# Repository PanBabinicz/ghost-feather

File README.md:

# Ghost Feather

> [!NOTE]
> **Please bear in mind that the workspace was primarily created for enjoyment
> and educational endeavors.**

> The MIT License (MIT)
>
> Copyright (c) 2011-2024 The Bootstrap Authors
>
> Permission is hereby granted, free of charge, to any person obtaining a copy
> of this software and associated documentation files (the "Software"), to deal
> in the Software without restriction, including without limitation the rights
> to use, copy, modify, merge, publish, distribute, sublicense, and/or sell
> copies of the Software, and to permit persons to whom the Software is
> furnished to do so, subject to the following conditions:
>
> The above copyright notice and this permission notice shall be included in
> all copies or substantial portions of the Software.
>
> THE SOFTWARE IS PROVIDED "AS IS", WITHOUT WARRANTY OF ANY KIND, EXPRESS OR
> IMPLIED, INCLUDING BUT NOT LIMITED TO THE WARRANTIES OF MERCHANTABILITY,
> FITNESS FOR A PARTICULAR PURPOSE AND NONINFRINGEMENT. IN NO EVENT SHALL THE
> AUTHORS OR COPYRIGHT HOLDERS BE LIABLE FOR ANY CLAIM, DAMAGES OR OTHER
> LIABILITY, WHETHER IN AN ACTION OF CONTRACT, TORT OR OTHERWISE, ARISING FROM,
> OUT OF OR IN CONNECTION WITH THE SOFTWARE OR THE USE OR OTHER DEALINGS IN
> THE SOFTWARE.

# Compilation process

> [!NOTE]
> **The current compilation process will be changed**

```console
~ arm-none-eabi-gcc -g -c -mfloat-abi=hard -mfpu=fpv4-sp-d16 -mcpu=cortex-m7 -mthumb \
                          -I memory -I bootloader \
                          startup/stm32f722xx/stm32722xx_startup.c -o build/stm32f722xx_startup.o
```

```console
~ arm-none-eabi-gcc -g -c -mfloat-abi=hard -mfpu=fpv4-sp-d16 -mcpu=cortex-m7 -mthumb \
                          -I libopencm3/include -I memory -DSTM32F7 \
                          bootloader/stm32f722xx_first_bootloader.c -o build/stm32f722xx_first_bootloader.o
```

```console
~ arm-none-eabi-as -g vectortable/stm32f722xx/stm32f722xx_vectortable.S -o build/stm32f722xx_vectortable.o
```

```console
~ arm-none-eabi-gcc -g -nostartfiles -nostdlib -mfloat-abi=hard -mfpu=fpv4-sp-d16 -mcpu=cortex-m7 -mthumb \
                       build/stm32f722xx_first_bootloader.o build/stm32f722xx_startup.o build/stm32f722xx_vectortable.o -o build/stm32f722xx_first_bootloader.elf \
                       -T linkerscript/stm32f722xx/stm32f722xx_bootloader.ld -L linkerscript/stm32f722xx -L libopencm3/lib -lopencm3_stm32f7
```

## CMake generators

> **Unix Makefiles**
>
> ```console
> ~ cmake -S . -B build -DCMAKE_TOOLCHAIN_FILE=arm-none-eabi-toolchain.cmake
> ~ cd build
> ~ cmake --build . --config Debug
> ```

> **Ninja Multi-Config**
>
> ```console
> ~ cmake -G "Ninja Multi-Config" -S . -B build -DCMAKE_TOOLCHAIN_FILE=arm-none-eabi-toolchain.cmake
> ~ cd build
> ~ cmake --build . --config Debug
> ```

> **CMake Presets**
>
> ```console
> ~ cmake --preset list
> ~ cmake --preset <build-type>
> ```

> **Build shell script**
>
> ```console
> ~ ./build.sh <build-type>
> ```

# How to program

> For now, CMake generates two elf files. Each of these files needs to be uploaded to the device.

# Newlib

> To use newlib with libopencm3 it is necessary to recomplie the libc to be able to use hard floating point numbers which use on-chip FPU.
> The second option is to use soft floating point numbers but the speed will be slower.

# Marco Paland printf implementation

> The Marco Paland printf implementation is a lightweight, standalone alternative designed
> specifically to address these limitations. This implementation offers a small memory footprint,
> portability, and independence from the full C standard library. It is widely used in embedded
> projects where developers require formatted output but cannot afford the code size and
> dependencies of a complete libc implementation.

# DFU script

> **Description**
>
> The script enables firmware update over USART. It allows users to upload binary firmware files to microcontroller-based devices with minimal effort.
> The script handles communication setup, data formatting, and transmission to ensure reliable updates.

> **Usage**
>
> ```console
> ~ python3 dfu_usart.py <binary> <port> <baudrate>
> ```
>
> - `<binary>`:   The firmware to be uploaded.
> - `<port>`:     The name of the serial port connected to the target device (e.g., /dev/tty.usbmodem).
> - `<baudrate>`: The communication speed in bits per second (e.g., 9600, 115200).

# SOCAT tool

> **Usage**
>
> ```console
> ~ socat -d -d PTY,raw,echo=0 PTY,raw,echo=0
> ~ stty -f /dev/ttysxxx 115200
> ~ screen /dev/ttysxxx 115200
> ```

# Unit tests

> **Description**
>
> The unit tests verify the functionality, reliability, and error handling of embedded system controllers using Google Test (GTest).
>
> They cover various scenarios, including:
> - Core functionality validation.
> - Boundary condition testing.
> - Error handling and fault tolerance.
> - Performance and efficiency checks.

> **Usage**
>
> ```console
> ~ cmake -G "Ninja" -S . -B build -DPROJECT_ROOT_DIR=$(pwd)/../..
> ~ cmake --build build
> ~ cd build && ctest
> ```

# Conda

## What is Conda?

> Conda is an open-source **package manager and environment manager** used for installing, running, and
> updating software packages and their dependencies. It is widely used in data science, machine learning,
> and scientific computing because it simplifies managing complex software environments.
>
> Unlike `pip`, which only installs Python packages, **Conda can manage packages written in multiple languages**
> (such as Python, R, and C libraries) and handles system-level dependencies as well.
>
> Conda is distributed with platforms such as:

- **Anaconda** – a large distribution that includes many preinstalled scientific packages.
- **Miniconda** – a lightweight version that installs only Conda and Python.

## Why Use Conda?

> Conda helps solve common development problems:

- **Dependency management** – automatically installs required libraries.
- **Environment isolation** – different projects can use different package versions.
- **Cross-language support** – works with Python, R, and other tools.
- **Reproducibility** – environments can be exported and recreated.

> Example: one project may require `Python 3.9` while another requires `Python 3.11`. Conda allows both to
> coexist without conflicts.

## Creating an Environment

> A Conda environment is an isolated workspace containing its own Python version and installed packages.
>
> Create a new environment:

```bash
conda create -n myenv python=3.10
```

Here:
- `-n myenv` specifies the environment name
- `python=3.10` installs a specific Python version

## Activating an Environment

> Before using an environment, it must be activated.

```bash
conda activate myenv
```

> After activation, all installed packages and Python commands will come from this environment.
>
> To deactivate:

```bash
conda deactivate
```

## Installing Packages

> Packages can be installed directly into the active environment.

```bash
conda install numpy pandas matplotlib
```

> Conda will automatically resolve and install required dependencies.

## Listing Environments

> To see all available environments:

```bash
conda env list
```

> or:

```bash
conda info --envs
```

## Removing an Environment

> If an environment is no longer needed, it can be deleted:

```bash
conda remove -n myenv --all
```

## Exporting an Environment

> To share or reproduce an environment:

```bash
conda env export > environment.yml
```

> This file can later be used to recreate the same environment.

## Recreating an Environment

```bash
conda env create -f environment.yml
```

> This installs all packages and dependencies exactly as defined in the exported file.

## EASTER EGG!

> CBR 929 broke. We have to repair it. I will do todays job tomorrow.

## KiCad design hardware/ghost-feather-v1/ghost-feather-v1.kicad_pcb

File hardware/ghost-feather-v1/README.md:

# Ghost Feather - hardware

## PCB used materials

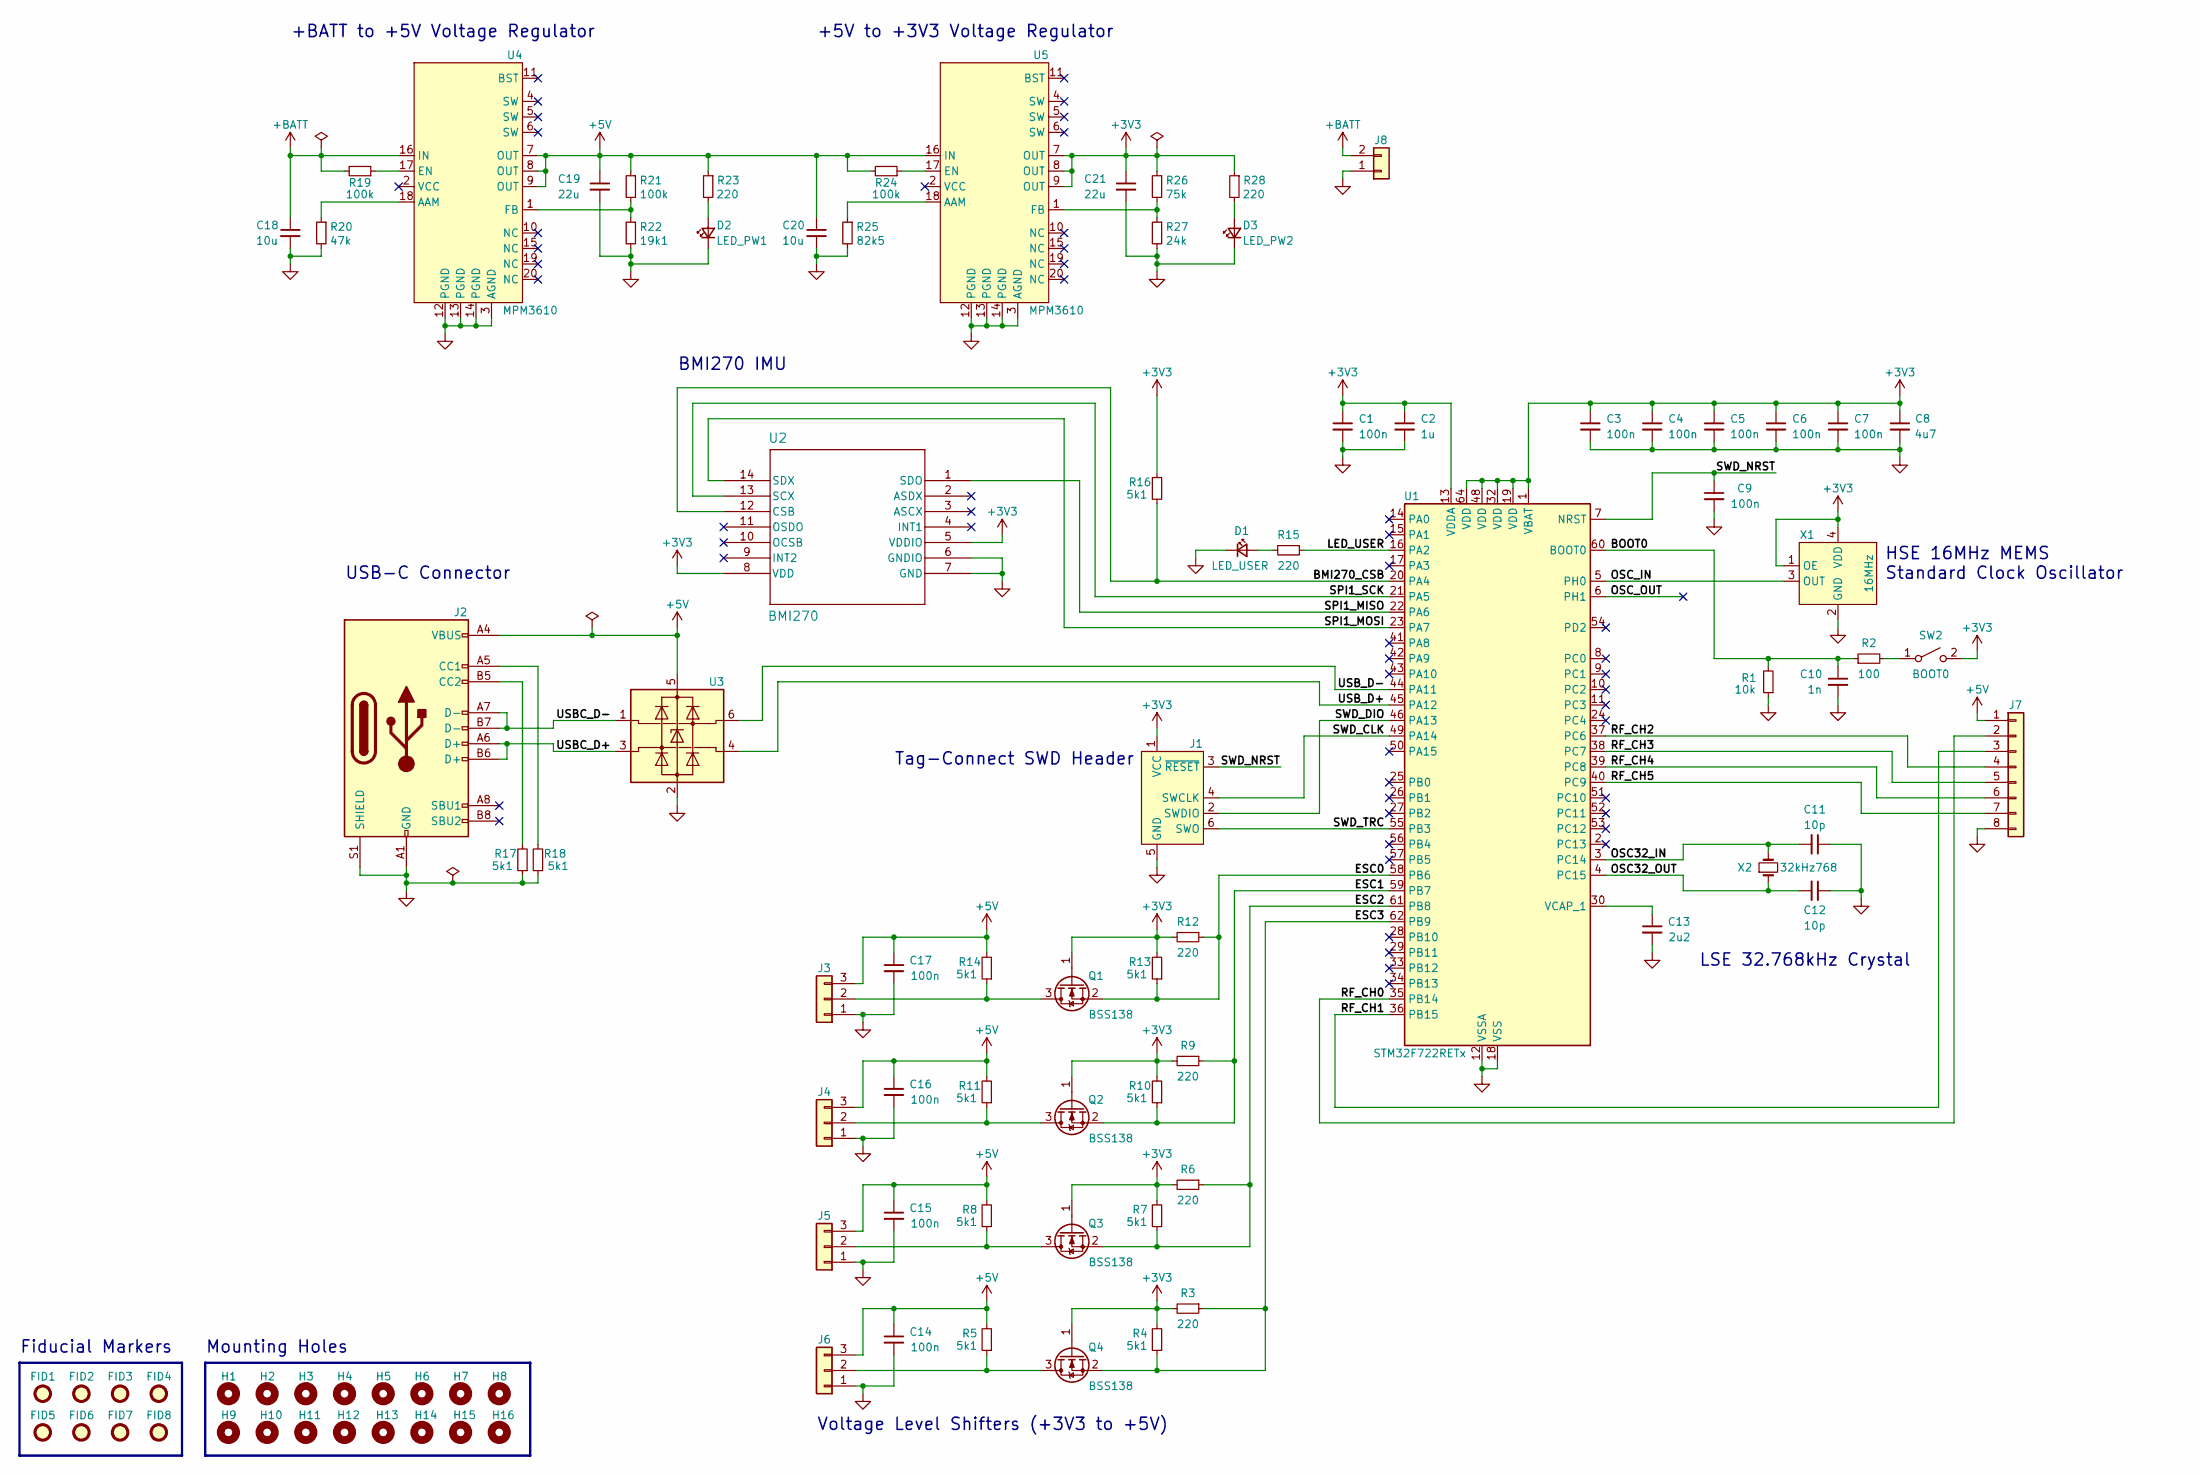
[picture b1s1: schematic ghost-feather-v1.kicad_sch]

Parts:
C1, C3, C4, C5, C6, C7, C9, C14, C15, C16, C17: 100n; C_0402_1005Metric
C2: 1u; C_0603_1608Metric
C8: 4u7; C_0603_1608Metric
C10: 1n; C_0402_1005Metric
C11, C12: 10p; C_0402_1005Metric
C13: 2u2; C_0603_1608Metric
C18, C20: 10u; C_0603_1608Metric
C19, C21: 22u; C_0603_1608Metric
D1: LED_USER; LED_0402_1005Metric; Manufacturer Part Number SML-P11VTT86R
D2: LED_PW1; LED_0402_1005Metric; Manufacturer Part Number SML-P11VTT86R
D3: LED_PW2; LED_0402_1005Metric; Manufacturer Part Number SML-P11VTT86R
FID1, FID2, FID3, FID4, FID5, FID6, FID7, FID8: Fiducial; Fiducial_1.5mm_Mask4.5mm
H1, H2, H3, H4, H5, H6, H7, H8, H9, H10, H11, H12, H13, H14, H15, H16: MountingHole; MountingHole_2.7mm_M2.5
J1: Conn_ARM_SWD_TagConnect_TC2030; Tag-Connect_TC2030-IDC-FP_2x03_P1.27mm_Vertical
J2: USB_C_Receptacle_USB2.0; USB_C_Receptacle_GCT_USB4105-xx-A_16P_TopMnt_Horizontal
J3, J4, J5, J6: Conn_01x03; Molex_PicoBlade_53048-0310_1x03_P1.25mm_Horizontal; Manufacturer Part Number 53048-0310
J7: Conn_01x08; Molex_PicoBlade_53048-0810_1x08_P1.25mm_Horizontal; Manufacturer Part Number 53048-0810
J8: Conn_01x02; AMASS_XT60PW-M_1x02_P7.20mm_Horizontal
Q1, Q2, Q3, Q4: BSS138; SOT-23
R1: 10k; R_0402_1005Metric
R2: 100; R_0402_1005Metric
R3, R6, R9, R12, R15, R23, R28: 220; R_0402_1005Metric
R4, R5, R7, R8, R10, R11, R13, R14, R16, R17, R18: 5k1; R_0402_1005Metric
R19, R21, R24: 100k; R_0402_1005Metric
R20: 47k; R_0402_1005Metric
R22: 19k1; R_0402_1005Metric
R25: 82k5; R_0402_1005Metric
R26: 75k; R_0402_1005Metric
R27: 24k; R_0402_1005Metric
SW2: BOOT0; SW_SPST_EVQPE1
U1: STM32F722RETx; LQFP-64_10x10mm_P0.5mm; Manufacturer Part Number STM32F722RET6
U2: BMI270; BMI270_BOS; Manufacturer Part Number BMI270
U3: USBLC6-2SC6_MOD; SOT-23-6; Manufacturer Part Number USBLC6-2SC6
U4, U5: MPM3610
X1: 16MHz; AMPMGFB_1.6mm1.2mm_16MHz; Manufacturer Part Number AMPMGFB-16.0000T
X2: 32kHz768; CC4V-T1A-32.768kHz; Manufacturer Part Number CC4V-T1A-32.768kHz-10pF-20PPM-TA-QC

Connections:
+3V3: C1.1, C2.1, C3.1, C4.1, C5.1, C6.1, C7.1, C8.1, C21.1, J1.1 (VCC), Q1.1 (G), Q2.1 (G), Q3.1 (G), Q4.1 (G), R3.2, R4.2, R6.2, R7.2, R9.2, R10.2, R12.2, R13.2, R16.2, R26.1, R28.1, SW2.2 (B), U1.1 (VBAT), U1.13 (VDDA), U1.19 (VDD), U1.32 (VDD), U1.48 (VDD), U1.64 (VDD), U2.5 (VDDIO), U2.8 (VDD), U5.7 (OUT), U5.8 (OUT), U5.9 (OUT), X1.1 (OE), X1.4 (VDD)
+5V: C14.1, C15.1, C16.1, C17.1, C19.1, C20.1, J2.A4 (VBUS), J2.A9 (VBUS), J2.B4 (VBUS), J2.B9 (VBUS), J3.3, J4.3, J5.3, J6.3, J7.1, R5.2, R8.2, R11.2, R14.2, R21.1, R23.1, R24.2, U3.5 (VBUS), U4.7 (OUT), U4.8 (OUT), U4.9 (OUT), U5.16 (IN)
+BATT: C18.1, J8.2, R19.2, U4.16 (IN)
/BMI270_CSB: R16.1, U1.20 (PA4), U2.12 (CSB)
/BOOT0: C10.1, R1.2, R2.1, U1.60 (BOOT0)
/ESC0: Q1.2 (S), R12.1, R13.1, U1.58 (PB6)
/ESC1: Q2.2 (S), R9.1, R10.1, U1.59 (PB7)
/ESC2: Q3.2 (S), R6.1, R7.1, U1.61 (PB8)
/ESC3: Q4.2 (S), R3.1, R4.1, U1.62 (PB9)
/LED_USER: R15.1, U1.16 (PA2)
/OSC32_IN: C11.2, U1.3 (PC14), X2.2
/OSC32_OUT: C12.2, U1.4 (PC15), X2.1
/OSC_IN: U1.5 (PH0), X1.3 (OUT)
/OSC_OUT: U1.6 (PH1)
/RF_CH0: J7.2, U1.35 (PB14)
/RF_CH1: J7.3, U1.36 (PB15)
/RF_CH2: J7.4, U1.37 (PC6)
/RF_CH3: J7.5, U1.38 (PC7)
/RF_CH4: J7.6, U1.39 (PC8)
/RF_CH5: J7.7, U1.40 (PC9)
/SPI1_MISO: U1.22 (PA6), U2.1 (SDO)
/SPI1_MOSI: U1.23 (PA7), U2.14 (SDX)
/SPI1_SCK: U1.21 (PA5), U2.13 (SCX)
/SWD_CLK: J1.4 (SWCLK), U1.49 (PA14)
/SWD_DIO: J1.2 (SWDIO), U1.46 (PA13)
/SWD_NRST: C9.1, J1.3 (~RESET), U1.7 (NRST)
/SWD_TRC: J1.6 (SWO), U1.55 (PB3)
/USBC_D+: J2.A6 (D+), J2.B6 (D+), U3.3 (I/O1)
/USBC_D-: J2.A7 (D-), J2.B7 (D-), U3.1 (I/O1)
/USB_D+: U1.45 (PA12), U3.4 (I/O2)
/USB_D-: U1.44 (PA11), U3.6 (I/O2)
GND: C1.2, C2.2, C3.2, C4.2, C5.2, C6.2, C7.2, C8.2, C9.2, C10.2, C11.1, C12.1, C13.2, C14.2, C15.2, C16.2, C17.2, C18.2, C19.2, C20.2, C21.2, D1.1 (K), D2.1 (K), D3.1 (K), J1.5 (GND), J2.A1 (GND), J2.A12 (GND), J2.B1 (GND), J2.B12 (GND), J2.S1 (SHIELD), J3.1, J4.1, J5.1, J6.1, J7.8, J8.1, R1.1, R17.1, R18.1, R20.2, R22.2, R25.2, R27.2, U1.12 (VSSA), U1.18 (VSS), U1.31 (VSS), U1.47 (VSS), U1.63 (VSS), U2.6 (GNDIO), U2.7 (GND), U3.2 (GND), U4.3 (AGND), U4.12 (PGND), U4.13 (PGND), U4.14 (PGND), U5.3 (AGND), U5.12 (PGND), U5.13 (PGND), U5.14 (PGND), X1.2 (GND)
unnamed: D1.2 (A), R15.2
unnamed: D2.2 (A), R23.2
unnamed: D3.2 (A), R28.2
unnamed: J2.A5 (CC1), R18.2
unnamed: J2.B5 (CC2), R17.2
unnamed: J3.2, Q1.3 (D), R14.1
unnamed: J4.2, Q2.3 (D), R11.1
unnamed: J5.2, Q3.3 (D), R8.1
unnamed: J6.2, Q4.3 (D), R5.1
unnamed: R2.2, SW2.1 (A)
unnamed: C13.1, U1.30 (VCAP_1)
unnamed: R20.1, U4.18 (AAM)
unnamed: R19.1, U4.17 (EN)
unnamed: R21.2, R22.1, U4.1 (FB)
unnamed: R25.1, U5.18 (AAM)
unnamed: R24.1, U5.17 (EN)
unnamed: R26.2, R27.1, U5.1 (FB)

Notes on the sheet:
HSE 16MHz MEMS Standard Clock Oscillator
Tag-Connect SWD Header
BMI270 IMU
LSE 32.768kHz Crystal
USB-C Connector
Voltage Level Shifters (+3V3 to +5V)
+5V to +3V3 Voltage Regulator
+BATT to +5V Voltage Regulator
Fiducial Markers
Mounting Holes

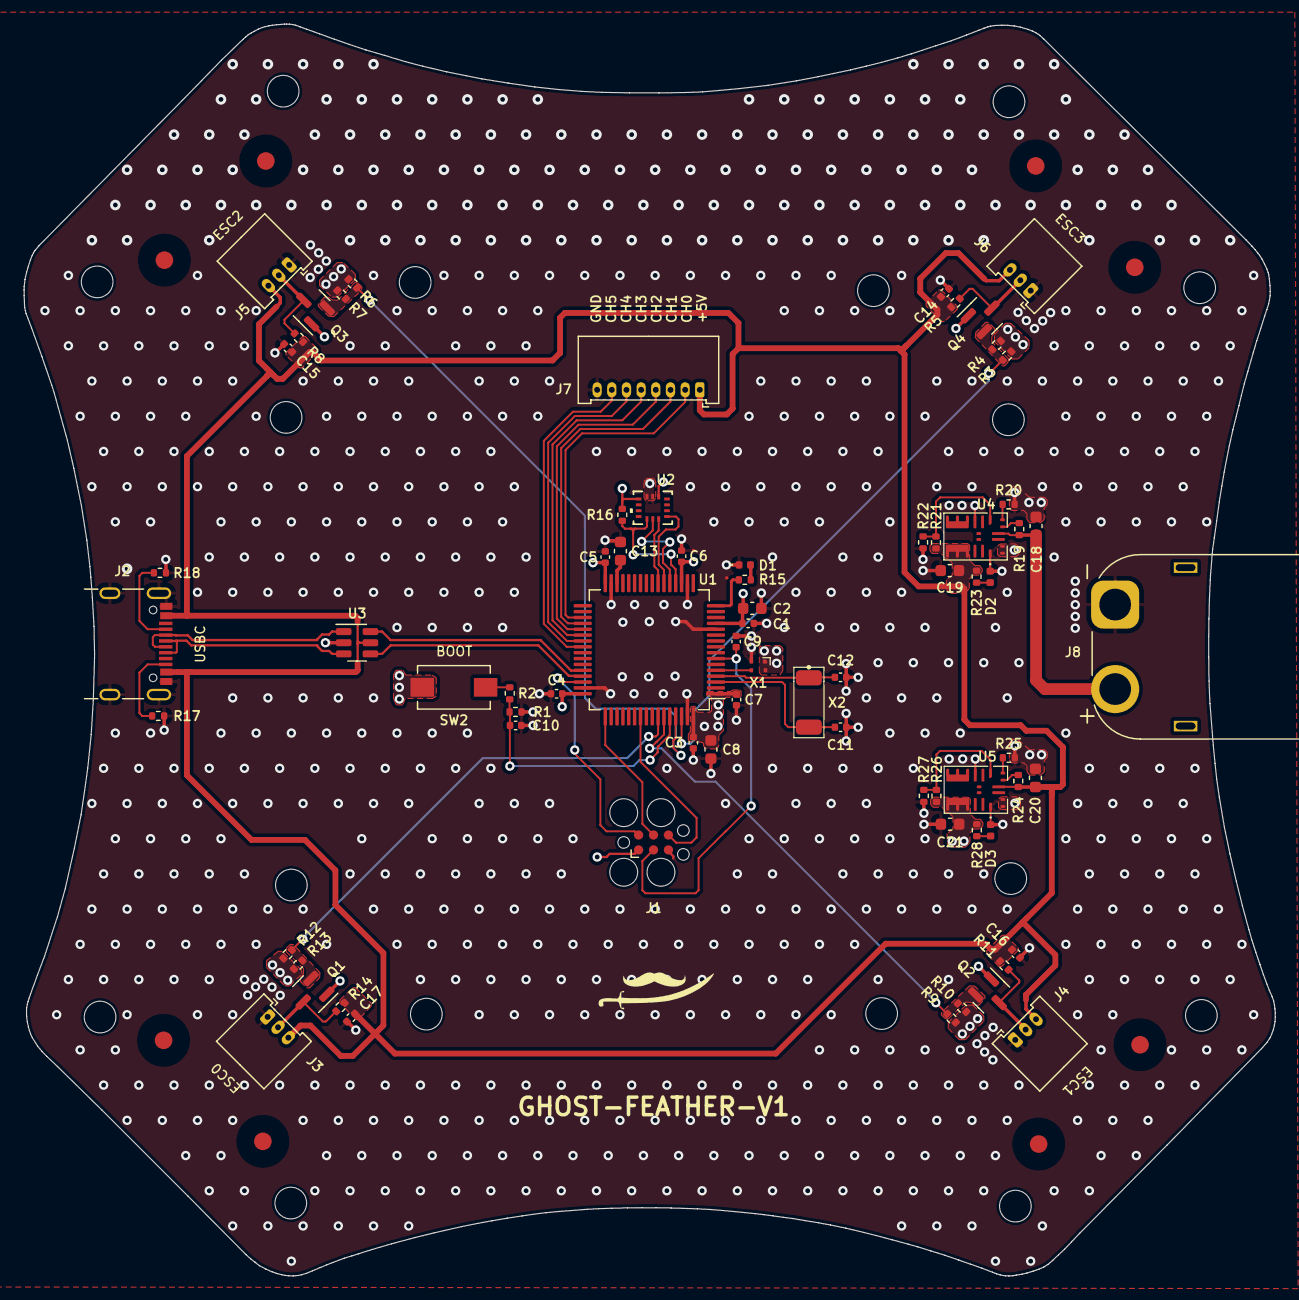
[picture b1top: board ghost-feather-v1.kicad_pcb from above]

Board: 4 copper layers, 106.6 x 106.7 mm, 96 parts (0 on the bottom side), 48 nets.

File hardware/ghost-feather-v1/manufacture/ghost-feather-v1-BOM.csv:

"Designator","Quantity","Value","Footprint","Description","Manufaturer","Manufaturer Part Number","Distributor Link"
"C1, C3, C4, C5, C6, C7, C9, C14, C15, C16, C17","11","100n","Capacitor_SMD:C_0402_1005Metric","Unpolarized capacitor, small symbol","","","",""
"C2","1","1u","Capacitor_SMD:C_0603_1608Metric","Unpolarized capacitor, small symbol","","","",""
"C8","1","4u7","Capacitor_SMD:C_0603_1608Metric","Unpolarized capacitor, small symbol","","","",""
"C10","1","1n","Capacitor_SMD:C_0402_1005Metric","Unpolarized capacitor, small symbol","","","",""
"C11, C12","2","10p","Capacitor_SMD:C_0402_1005Metric","Unpolarized capacitor, small symbol","","","",""
"C13","1","2u2","Capacitor_SMD:C_0603_1608Metric","Unpolarized capacitor, small symbol","","","",""
"C18, C20","2","10u","Capacitor_SMD:C_0603_1608Metric","Unpolarized capacitor, small symbol","","","",""
"C19, C21","2","22u","Capacitor_SMD:C_0603_1608Metric","Unpolarized capacitor, small symbol","","","",""
"D1","1","LED_USER","LED_SMD:LED_0402_1005Metric","Light emitting diode, small symbol","ROHM Semiconductor","SML-P11VTT86R","https://eu.mouser.com/ProductDetail/ROHM-Semiconductor/SML-P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",""
"D2","1","LED_PW1","LED_SMD:LED_0402_1005Metric","Light emitting diode, small symbol","ROHM Semiconductor","SML-P11VTT86R","https://eu.mouser.com/ProductDetail/ROHM-Semiconductor/SML-P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",""
"D3","1","LED_PW2","LED_SMD:LED_0402_1005Metric","Light emitting diode, small symbol","ROHM Semiconductor","SML-P11VTT86R","https://eu.mouser.com/ProductDetail/ROHM-Semiconductor/SML-P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",""
"J2","1","USB_C_Receptacle_USB2.0","Connector_USB:USB_C_Receptacle_GCT_USB4105-xx-A_16P_TopMnt_Horizontal","USB 2.0-only Type-C Receptacle connector","","","",""
"J3, J4, J5, J6","4","Conn_01x03","Connector_Molex:Molex_PicoBlade_53048-0310_1x03_P1.25mm_Horizontal","Generic connector, single row, 01x03, script generated (kicad-library-utils/schlib/autogen/connector/)","Molex","53048-0310","https://eu.mouser.com/ProductDetail/Molex/53048-0310?qs=zXrb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",""
"J7","1","Conn_01x08","Connector_Molex:Molex_PicoBlade_53048-0810_1x08_P1.25mm_Horizontal","Generic connector, single row, 01x08, script generated (kicad-library-utils/schlib/autogen/connector/)","Molex","53048-0810","https://eu.mouser.com/ProductDetail/Molex/53048-0810?qs=KHty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",""
"J8","1","Conn_01x02","Connector_AMASS:AMASS_XT60PW-M_1x02_P7.20mm_Horizontal","Generic connector, single row, 01x02, script generated (kicad-library-utils/schlib/autogen/connector/)","","","",""
"Q1, Q2, Q3, Q4","4","BSS138","Package_TO_SOT_SMD:SOT-23","50V Vds, 0.22A Id, N-Channel MOSFET, SOT-23","","","",""
"R1","1","10k","Resistor_SMD:R_0402_1005Metric","Resistor, small symbol","","","",""
"R2","1","100","Resistor_SMD:R_0402_1005Metric","Resistor, small symbol","","","",""
"R3, R6, R9, R12, R15, R23, R28","7","220","Resistor_SMD:R_0402_1005Metric","Resistor, small symbol","","","",""
"R4, R5, R7, R8, R10, R11, R13, R14, R16, R17, R18","11","5k1","Resistor_SMD:R_0402_1005Metric","Resistor, small symbol","","","",""
"R19, R21, R24","3","100k","Resistor_SMD:R_0402_1005Metric","Resistor, small symbol","","","",""
"R20","1","47k","Resistor_SMD:R_0402_1005Metric","Resistor, small symbol","","","",""
"R22","1","19k1","Resistor_SMD:R_0402_1005Metric","Resistor, small symbol","","","",""
"R25","1","82k5","Resistor_SMD:R_0402_1005Metric","Resistor, small symbol","","","",""
"R26","1","75k","Resistor_SMD:R_0402_1005Metric","Resistor, small symbol","","","",""
"R27","1","24k","Resistor_SMD:R_0402_1005Metric","Resistor, small symbol","","","",""
"SW2","1","BOOT0","Button_Switch_SMD:SW_SPST_EVQPE1","Single Pole Single Throw (SPST) switch","","","",""
"U1","1","STM32F722RETx","Package_QFP:LQFP-64_10x10mm_P0.5mm","STMicroelectronics Arm Cortex-M7 MCU, 512KB flash, 256KB RAM, 216 MHz, 1.7-3.6V, 50 GPIO, LQFP64","STMicroelectronics","STM32F722RET6","https://eu.mouser.com/ProductDetail/STMicroelectronics/STM32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",""
"U2","1","BMI270","ghost-feather-v1:BMI270_BOS","","Bosch Sensortec","BMI270","https://eu.mouser.com/ProductDetail/Bosch-Sensortec/BMI270?q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",""
"U3","1","USBLC6-2SC6_MOD","Package_TO_SOT_SMD:SOT-23-6","Very low capacitance ESD protection diode, 2 data-line, SOT-23-6","STMicroelectronics","USBLC6-2SC6","https://eu.mouser.com/ProductDetail/STMicroelectronics/USBLC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",""
"U4, U5","2","MPM3610","ghost-feather-v1:MPM3610","","","","",""
"X1","1","16MHz","ghost-feather-v1:AMPMGFB_1.6mm1.2mm_16MHz","","ABRACON","AMPMGFB-16.0000T","https://eu.mouser.com/ProductDetail/ABRACON/AMPMGFB-16.0000T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",""
"X2","1","32kHz768","ghost-feather-v1:CC4V-T1A-32.768kHz","Two pin crystal, small symbol","Micro Crystal","CC4V-T1A-32.768kHz-10pF-20PPM-TA-QC","https://eu.mouser.com/ProductDetail/Micro-Crystal/CC4V-T1A-3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",""

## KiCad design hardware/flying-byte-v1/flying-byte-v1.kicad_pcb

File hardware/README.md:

# Hardware

## Important links

> Phil's lab
>
> Bluetooth Hardware Design  
> https://www.youtube.com/watch?v=nkHFoxe0mrU&ab_channel=Phil%E2%80%99sLab  
> https://www.youtube.com/watch?v=PlXd3lLZ4vc&t=16s&ab_channel=Phil%E2%80%99sLab

> Over-the-Air DFU procedure
>
> https://onlinedocs.microchip.com/oxy/GUID-26457D23-798C-47B0-9F40-C5DA6E995C6F-en-US-2/GUID-79B3231C-7BD0-4459-80A5-A198A4F1B366.html

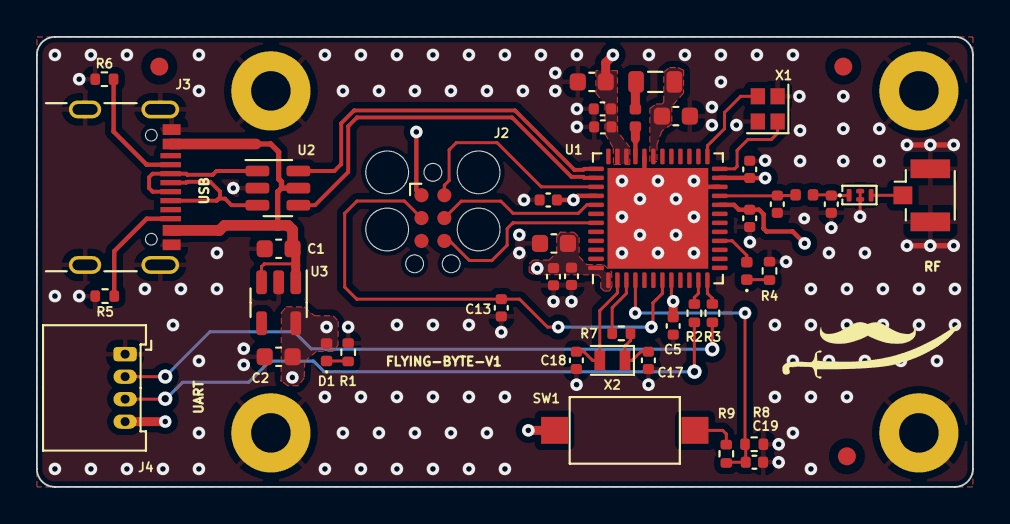
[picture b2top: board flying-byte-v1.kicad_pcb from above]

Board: 4 copper layers, 52.0 x 25.0 mm, 51 parts (0 on the bottom side), 33 nets.

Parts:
C1, C2, C3, C10, C14: 4u7; C_0603_1608Metric
C4, C5, C6, C7, C8, C9, C11, C12, C13, C19: 100n; C_0402_1005Metric
C15: 0p8; C_0402_1005Metric
C16: 0p3; C_0402_1005Metric
C17, C18: 10p; C_0402_1005Metric
D1, D2: LED; LED_0402_1005Metric
FLT1: DLF162500LT-5028A1
FM1, FM2, FM3: Fiducial; Fiducial_1mm_Mask2mm
H1, H2, H3, H4: MountingHole_Pad; MountingHole_2.2mm_M2_Pad
J1: Conn_Coaxial; U.FL_Hirose_U.FL-R-SMT-1_Vertical
J2: Conn_ARM_SWD_TagConnect_TC2030; Tag-Connect_TC2030-IDC-FP_2x03_P1.27mm_Vertical
J3: USB_C_Receptacle_USB2.0; USB_C_Receptacle_GCT_USB4105-xx-A_16P_TopMnt_Horizontal
J4: Conn_01x04; Molex_PicoBlade_53048-0410_1x04_P1.25mm_Horizontal
L1: 10n; L_0402_1005Metric
L2: 10u; L_0805_2012Metric
L3: 2n7; L_0402_1005Metric
R1, R2, R3, R4, R9: 220R; R_0402_1005Metric
R5, R6, R8: 5k1; R_0402_1005Metric
R7: 0; R_0402_1005Metric
SW1: SW_Push; SW_SPST_CK_RS282G05A3
U1: STM32WB55CEU6; QFN-48-1EP_7x7mm_P0.5mm_EP5.6x5.6mm
U2: USBLC6-2SC6_MOD; SOT-23-6
U3: MIC5365-3.3YD5; SOT-23-5
X1: 32MHz; Crystal_SMD_2016-4Pin_2.0x1.6mm
X2: 32kHz768; Crystal_SMD_2012-2Pin_2.0x1.2mm

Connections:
+3V3: C2.1, C3.1, C4.1, C5.1, C6.1, C7.1, C8.1, C9.1, C10.1, C11.1, C12.1, D1.2 (A), J2.1 (VCC), J4.4, SW1.2, U1.1 (VBAT), U1.8 (VDDA), U1.20 (VDD), U1.23 (VDDRF), U1.34 (VDDSMPS), U1.35 (VDD), U1.40 (VDDUSB), U1.48 (VDD), U3.5 (VOUT)
+5V: C1.1, J3.A4 (VBUS), J3.A9 (VBUS), J3.B4 (VBUS), J3.B9 (VBUS), U2.5 (VBUS), U3.1 (VIN), U3.3 (EN)
/BOOT0: C19.1, R8.1, R9.1, U1.4 (PH3)
/BOOT0_SW: R9.2, SW1.1
/HSE_IN: U1.25 (OSC_IN), X1.3
/HSE_OUT: U1.24 (OSC_OUT), X1.1
/LED_A: D2.2 (A), U1.16 (PA7)
/LED_K: D2.1 (K), R4.2
/LSE_IN: C18.1, U1.2 (PC14), X2.2
/LSE_OUT: R7.1, U1.3 (PC15)
/LSE_OUT_R: C17.1, R7.2, X2.1
/RF: C15.1, L3.1, U1.21 (RF1)
/RF_ANT: FLT1.3 (OUT), J1.1 (In)
/RF_MATCH: C16.1, FLT1.1 (IN), L3.2
/SMPS_L: L1.2, L2.1
/SMPS_VFB: C14.1, L2.2, U1.31 (VFBSMPS)
/SMPS_VLX: L1.1, U1.33 (VLXSMPS)
/SWD_CLK: J2.4 (SWCLK), U1.41 (PA14)
/SWD_DIO: J2.2 (SWDIO), U1.39 (PA13)
/SWD_NRST: C13.1, J2.3 (~RESET), U1.7 (NRST)
/SWD_TRC: J2.6 (SWO), U1.43 (PB3)
/UART_RX: R3.2, U1.12 (PA3)
/UART_RXC: J4.2, R3.1
/UART_TX: R2.2, U1.11 (PA2)
/UART_TXC: J4.3, R2.1
/USBC_CC1: J3.A5 (CC1), R6.1
/USBC_CC2: J3.B5 (CC2), R5.1
/USBC_D+: J3.A6 (D+), J3.B6 (D+), U2.3 (I/O1)
/USBC_D-: J3.A7 (D-), J3.B7 (D-), U2.1 (I/O1)
/USB_D+: U1.38 (PA12), U2.4 (I/O2)
/USB_D-: U1.37 (PA11), U2.6 (I/O2)
GND: C1.2, C2.2, C3.2, C4.2, C5.2, C6.2, C7.2, C8.2, C9.2, C10.2, C11.2, C12.2, C13.2, C14.2, C15.2, C16.2, C17.2, C18.2, C19.2, FLT1.2 (GND), FLT1.4 (GND), H1.1, H2.1, H3.1, H4.1, J1.2 (Ext), J2.5 (GND), J3.A1 (GND), J3.A12 (GND), J3.B1 (GND), J3.B12 (GND), J3.S1 (SHIELD), J4.1, R1.1, R4.1, R5.2, R6.2, R8.2, U1.22 (VSSRF), U1.32 (VSSSMPS), U1.49 (VSS), U2.2 (GND), U3.2 (GND), X1.2, X1.4
unnamed: D1.1 (K), R1.2

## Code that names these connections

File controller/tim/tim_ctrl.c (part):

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///
/// Used timers inside ghost feather system:
///
/// MOTOR0 -> TIM4_CH4  (PB9)   gp4_16
/// MOTOR1 -> TIM4_CH3  (PB8)   gp4_16
/// MOTOR2 -> TIM4_CH2  (PB7)   gp4_16
/// MOTOR3 -> TIM4_CH1  (PB6)   gp4_16
///
/// RFCH1  -> TIM12_CH1 (PB14)  gp2
/// RFCH2  -> TIM12_CH2 (PB15)  gp2
/// RFCH3  -> TIM8_CH1  (PC6)   adv4
/// RFCH4  -> TIM8_CH2  (PC7)   adv4
/// RFCH5  -> TIM8_CH3  (PC8)   adv4
/// RFCH6  -> TIM8_CH4  (PC9)   adv4
///
///  ----------------------------
/// |                    BAT |*+-|
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
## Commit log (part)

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2025-08-06 feat: Add bmi270 gyr_get_y procedure and null pointer protection unit tests
2025-08-07 feat: Add bmi270 acc_get_x procedure and null pointer protection unit tests
2025-08-07 feat: Add bmi270 acc_get_z procedure and null pointer protection unit tests
2025-08-08 feat: Add bmi270 acc_get_z procedure and null pointer protection unit tests. Previous commit adds set function
2025-08-09 feat: Add bmi270 stat_get procedure and null pointer protection unit tests
2025-08-10 feat: Add bmi270 gyr_read null pointer protection unit test
2025-08-12 feat: Add bmi270 gyr_slf_tst null pointer protection unit test
2025-08-13 fix: Change name of the gpio port enums
2025-08-14 feat: Implement the spi_read and spi_send mock functions
2025-08-17 feat: Remove const qualifier from spi_ctrl_get_dev function. Add bmi270_spi_ctrl_asg function
2025-08-18 feat: Add bmi270 gyr_read procedure unit test
2025-08-20 feat: Add bmi270 time_read procedure unit test
2025-08-22 feat: Add bmi270 spi_ctrl_asg procedure and null pointer protection unit tests
2025-08-25 feat: Add bmi270 pwr_mode_set null pointer protection unit test
2025-08-26 fix: Apply new bmi270_pwr_mode_get_conf function name to unit tests
2025-08-28 feat: Improve resources sharing inside bmi270_acc_get_x test fixture class
2025-08-28 feat: Improve resources sharing inside bmi270_acc_read test fixture class
2025-08-29 feat: Improve resources sharing inside bmi270_acc_set_y test fixture class
2025-08-29 feat: Improve resources sharing inside bmi270_deinit test fixture class
2025-08-30 fix: Rename bmi270 get_dev unit test to dev_get
2025-08-30 feat: Improve resources sharing inside bmi270_gyr_get_z test fixture class
2025-08-30 feat: Improve resources sharing inside bmi270_gyr_set_x test fixture class
2025-08-31 feat: Improve resources sharing inside bmi270_gyr_slf_tst test fixture class
2025-08-31 feat: Improve resources sharing inside bmi270_pwr_mode_get_conf test fixture class
2025-09-01 feat: Improve resources sharing inside bmi270_soft_rst test fixture class
2025-09-01 feat: Improve resources sharing inside bmi270_stat_get test fixture class
2025-09-01 feat: Improve resources sharing inside bmi270_temp_read test fixture class
2025-09-01 feat: Improve resources sharing inside bmi270_time_get test fixture class
2025-09-01 feat: Improve resources sharing inside bmi270_time_set test fixture class
2025-09-03 fix: Adjust tx_idx inside SetUp and TearDown for acc_read, gyr_read, temp_read and time_read unit tests
2025-09-04 fix: Change spi_dr buffer size to 0x4000, adjust tx_idx and rx_idx variables types
2025-09-06 fix: Change spi_dr buffer size to 0x8000
2025-09-07 fix: Remove unnecessary else statements from bmi270_pwr_mode_set function
2025-09-09 fix: Apply changes related to SOLID principles to bmi270_init function. Change spi_ctrl_dev_get function to simpler one
2025-09-11 refactor: Change dev shared resource to bmi270 in acc_get_xyz functions
2025-09-12 refactor: Change dev shared resource to bmi270 in acc_slf_tst functions
2025-09-12 refactor: Change dev shared resource to bmi270 in dev_get functions
2025-09-13 refactor: Change dev shared resource to bmi270 in gyr_read function
2025-09-13 refactor: Change dev shared resource to bmi270 in gyr_slf_tst function
2025-09-14 refactor: Change dev shared resource to bmi270 in spi_ctrl_asg function
2025-09-14 refactor: Change dev shared resource to bmi270 in temp related functions
2025-09-15 feat: Add bmi270 pwr_mode_set procedure unit test #1
2025-09-17 feat: Add spi_ctrl device as shared resource to bmi270 acc_slf_tst unit test
2025-09-19 fix: Align the spaces inside acc_slf_tst unit test
2025-09-20 feat: Add bmi270 gyr_slf_tst procedure unit test
2025-09-21 doc: Add comments to static functions inside second_bootloader.c file
2025-09-24 debug: Add saved ozone project configurations that set PC in a good way
2025-09-25 fix: Adjust the GPIO setup inside first bootloader for blinking purpose
2025-09-28 refactor: Change first bootloader, second bootloader and boot updater to bootloader, apploader and updater to better readability
2025-09-29 feat: Add common systick delay function to ghost_feather_common.h file
2025-10-01 feat: Add led panic mode inside app obtained by use of systick
2025-10-03 feat: Add timing header and source file. Add first dwt related functions
2025-10-05 feat: Update root CMakeLists.txt and others to support timing feature
2025-10-05 feat: Update ozone configurations
2025-10-07 feat: Add build-type configuration to root CMakeLists.txt
2025-10-09 feat: Propagate compile option to app subdirectory
2025-10-09 feat: Propagate compile option to dfu subdirectory
2025-10-10 fix: Remove unused ghost_feather_common library from root CMakeLists.txt
2025-10-10 feat: Propagate compile option to startup subdirectory
2025-10-10 feat: Add system control space header file to timing
2025-10-12 doc: Add programming manual for stm32f7 and stm32h7 series cortex m7 processor
2025-10-15 fix: Remove bidioe function which has bug in it
2025-10-16 fix: Set FRXTH bit to 1/2 FIFO level. Remove bug related to wrong ssm functions
2025-10-18 doc: Change doxygen comments inside bmi270 multiple read/write functions
2025-10-20 feat: Add spi.h include inside bmi270 source file. Create self explanatory code inside bmi270 reg read/write functions
2025-10-23 feat: Add timing dwt functions to bmi270 module
2025-10-23 fix: Change the validation of the bmi270 config file function
2025-10-25 feat: Add bmi270 POR register value defines
2025-10-26 fix: Refactor the bmi270 init function #2
2025-10-28 fix: Refactor the bmi270 init function #3
2025-10-30 fix: Make stack bigger it resolves problem with bmi270 config file validation
2025-11-01 feat: Add APB2 frequency shared timing variable
2025-11-04 feat: Add APB1 frequency shared timing variable
2025-11-05 wip: Add is_init flags and information about mapped timers inside the system
2025-11-08 wip: Add advanced-control timers register definitions #2
2025-11-10 wip: Add general purpose timers register definitions #2
2025-11-12 feat: Create appropriate header files to store adv, base and gp tim register structures
2025-11-14 feat: Add gpx tim structures which holds all registers
2025-11-15 feat: Add tim ctrl common header file
2025-11-17 feat: Create base1 tim device structure used during init process
2025-11-19 feat: Add tim2345 por settings variable and deinit function
2025-11-21 feat: Add tim init and deinit functions prototypes
2025-11-22 feat: Add enable and disable gpx_tim2345 functions. Refactor tim_ctrl_gpx_timx code
2025-11-24 feat: Add tim10111314_por struct with deinit function. Adjust all tim register members to 32-bits
2025-11-25 feat: Add init, deinit, enable and disable function to tim_basex
2025-11-28 fix: Use proper names for structs and enums inside tim_ctrl_advx source file
2025-11-29 feat: Add TIM12 input capture device configuration inside tim_ctrl source file
2025-12-01 feat: Enable NVIC interrupt TIM8_CC
2025-12-03 feat: Add entry point to linkerscipts
2025-12-05 feat: Init tim_ctrl module inside application
2025-12-07 Fix: Adjust vectortable inside CMakeLists.txt root file
2025-12-08 fix: Mark _reset_handler as .word inside vectortable (fixes the linking problem)
2025-12-10 feat: Add the ccr_data struct and ccr_inst enum inside tim_ctrl_common. Append all related device structs
2025-12-12 feat: Add doxygen documentation inside tim_ctrl.c, tim_ctrl.h, tim_controller_common.h files
2025-12-13 feat: Add doxygen comments for TIM10-TIM14 registers
2025-12-15 feat: Add the doxygen comments for advanced timers (TIM1 and TIM8)
2025-12-17 feat: Add tim_ctrl_dev_arr_get function
2025-12-18 fix: Replace breif to brief inside comments
2025-12-21 feat: Add PID controller library to controller CMakeLists.txt files
2025-12-23 feat: Remove unused vectortable CMakeLists.txt
2025-12-26 fix: Remove TODOs from bootloader.c
2025-12-27 feat: Add application which tests the throttle response
2025-12-28 feat: Expand application size in linkerscript memory map
2025-12-30 feat: Add ghf_op structure which stores ghf status, launch and land steps
2026-01-01 wip: ref: TIM drivers
2026-01-02 wip: ref: Move BMI270 sensor to modules directory. Refactor TIM related files
2026-01-04 feat: Add vtol and motor libraries
2026-01-06 wip: Add Attitude and Heading Reference System module (ahrs) #1
2026-01-07 feat: Adjust vtol take-off and land procedure ranges
2026-01-10 feat: Add doxygen documentation for motor module
2026-01-11 feat: Add doxygen documentation for bmi270_spi driver.
2026-01-13 feat: Add doxygen documentation for tim module.
2026-01-14 feat: Add doxygen documentation for spi driver.
2026-01-18 fix: Delete controller and core dirs. Remove tim_ctrl related functions
2026-03-05 feat: Add --help option inside build.sh shell script
2026-03-08 doc: Add drone pictures to ghost feather hardware README.md
2026-03-09 doc: Rotate real pcb image. Add subchapters to the hardware README.md
2026-03-11 fix: Change the brief comment for cf_instace struct
2026-03-13 feat: wip: Add PID controller module #1
2026-03-15 feat: Update CMakeLists.txt files
2026-03-18 feat: Remove pointer passing from ll_spi_dev_init function. Add spi instance enum and device array
2026-03-20 feat: wip: Refactor ahrs module #1
2026-03-22 feat: Change passing instance as an argument to passing a pointer inside pid controller module
2026-03-23 feat: Finish complementary filter module
2026-03-26 feat: wip: Refactor the rc module #1
2026-03-27 feat: wip: Refactor the ahrs module #2
2026-03-29 feat: Finish PID controller
2026-03-30 feat: Ignore jdebug user files
2026-04-01 feat: Move calibration function inside ghf module. Use ghf_get to obtain an object from a singleton
2026-04-03 feat: Add emergency behavior when SWA is ON
2026-04-06 fix: Update argument name inside safe mode function
2026-04-07 feat: Make sure led is turned off after leaving safe mode
2026-04-08 doc: fix: Change the photo name to correct one
2026-04-09 doc: Add chapter related to tuning the PID gains using test stand
2026-04-13 feat: Add is_ready function inside ghf
2026-04-21 feat: hardware: Add ghost-feather-v2 kicad project. Finish power supply decoupling capacitors scheme for stm32f722xx
2026-04-23 feat: hardware: Add ghost-feather-v2 boot0 circuit
2026-04-25 feat: hardware: Add ghost-feather-v2 BMP390 sensor
2026-04-26 feat: hardware: wip: Add USB, SENSORS and MCU sectors on schematic
2026-04-29 feat: hardware: Add crystals for nRF52810. Add voltage level shifters for ESCs
2026-05-01 feat: hadware: wip: Add UBSC
2026-05-04 feat: hadware: Add STM32F7 HSE
2026-05-06 feat: software: wip: Add I2C low level driver #2
2026-05-09 fix: Some changes in README
2026-05-11 feat: software: wip: Add I2C low level driver #5. Adds init and deinit functions alongside with low lever i2c device structure
2026-05-12 feat: software: wip: Add I2C low level driver #7. Adds tramsmit and receive functions
2026-05-15 feat: software: wip: Add I2C low level driver #10. Adds I2C1-I2C3 addresses with MMIO macro and cr1 mask enum
2026-05-16 feat: software: wip: Add I2C low level driver #12. Adds oar1 and oar2 mask enums
2026-05-16 feat: software: wip: Add I2C low level driver #15. Adds pecr, rxdr and txdr mask enums
2026-05-17 feat: software: wip: Add I2C low level driver #17. TX/RX DMA enable/disable functions refactor
2026-05-19 feat: software: wip: Add I2C low level driver #20. Use MMIO32 from libopencm3 for clarity
2026-05-20 fix: software: wip: Add I2C low level driver #22. Remove ll_i2c_regs_por
2026-05-21 feat: software: wip: Add I2C low level driver #25. Adds dnf type
2026-05-22 feat: software: wip: Add I2C low level driver #27. Refactors interrupt enable/disable functions
2026-05-24 feat: software: wip: Add I2C low level driver #30. Add clock stretching enable/disable functions
2026-05-25 feat: software: wip: Add I2C low level driver #32. Adds general call enable/disablefunctions
2026-05-26 feat: software: wip: Add I2C low level driver #35. Adds alert enable/disablefunctions
2026-05-26 feat: software: wip: Add I2C low level driver #37. Adds slave address 7-bit and 10-bit set functions
2026-05-27 feat: software: wip: Add I2C low level driver #39. Adds start bit check if statement
2026-05-28 fix: software: wip: Add I2C low level driver #42. Use uppercase I2C in doxygen comments
2026-05-29 feat: software: wip: Add I2C low level driver #44. Adds shift enums
